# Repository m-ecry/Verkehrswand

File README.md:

# Verkehrswand
Einfache Anzeige für Ankunft und Abfahrt von einer Haltestelle mit Siebensegmentanzeigen und ein paar kleinen Extras.

- 2 Haltestellen
- 5 Linien
  - jeweils zwei Richtungen
  - Abfahrt in.., Nächste Abfahrt in..

Bauteilliste:
40x 7-Segmentanzeigen SC56-11GWA (Grün, 0,56") Common Cathode
40x Schieberegister SN74HC595
- pro Richtung 2x2 für Abfahrt in und nächste Abfahrt

1x Raspberry Pi (für Internetzugang, evtl. Austauschen durch Stromsparende Alternative)
X Knöpfe

Das ganze auf einer Holzplatte mit Abmaßen 75 x 55 cm, 5 cm hoch für Raum zum bestücken.
Jeden Tag ein wenig..
Und noch ein wenig..

SCHema und BoRDdateien, erstellt mit Eagle 7.7.0.
Enthalten Boardentwurf für 7-Segment Anzeige, angesteuert durch 2 74-595 Shift-Register. Nötige Anschlusskontaktierung: 
- Supply (1x GND, 1x VCC)
- SER
- CLK
- (optional) OE

Version A (doppelshift2): Standartversion mit Lötanschlüssen für Kontaktierung.

Version B (doppelshift2Bus): Kontaktierung über Flachbandkabel (6-adrig) dank Wannenstecker.

Idee für anderes Projekt: Pilzmonitor, Zeitschloss mit DC-Motor (Schrittmotor geeigneter?)

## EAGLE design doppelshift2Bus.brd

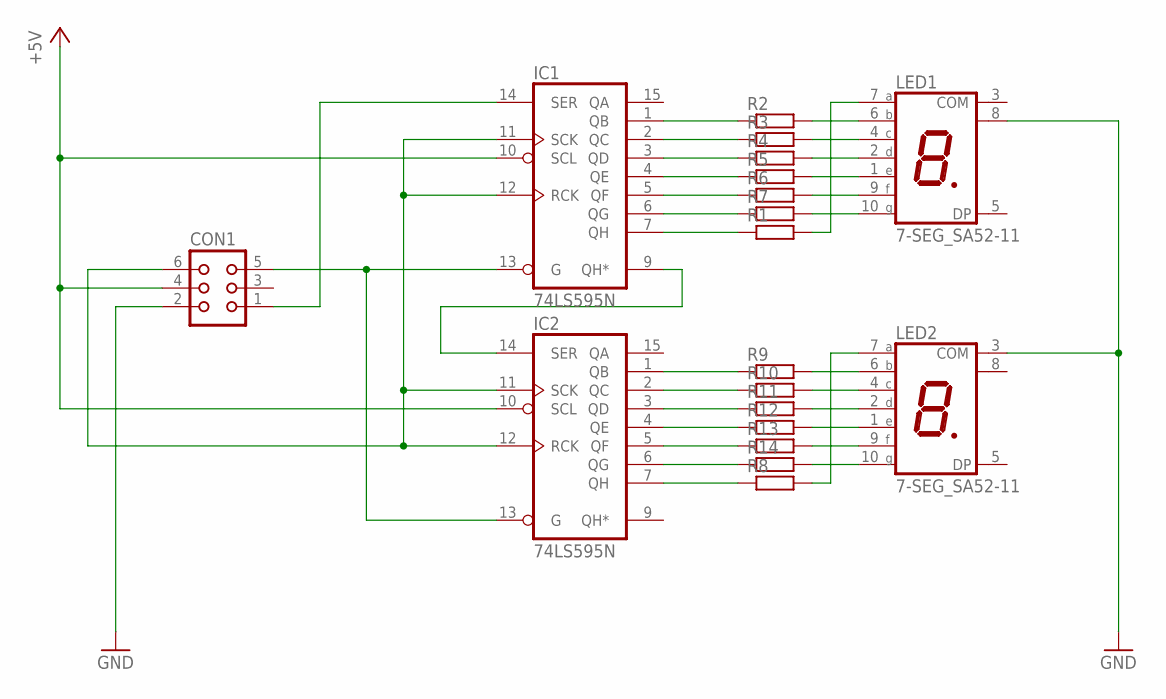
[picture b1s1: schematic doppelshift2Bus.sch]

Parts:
CON1: CON06L
IC1, IC2: 74LS595N; DIL16
LED1, LED2: 7-SEG_SA52-11; SA52-11
R1, R2, R3, R4, R5, R6, R7, R8, R9, R10, R11, R12, R13, R14: R-EU_0309/10; 0309/10

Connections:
CLK: CON1.6, IC1.11 (SCK), IC1.12 (RCK), IC2.11 (SCK), IC2.12 (RCK)
GND: CON1.2, IC1.8 (GND), IC2.8 (GND), LED1.8 (COM), LED2.3 (COM)
unnamed: IC2.7 (QH), R8.1
unnamed: IC1.1 (QB), R2.1
unnamed: IC1.2 (QC), R3.1
unnamed: IC1.3 (QD), R4.1
unnamed: IC1.4 (QE), R5.1
unnamed: IC1.5 (QF), R6.1
unnamed: IC1.6 (QG), R7.1
unnamed: LED2.7 (A), R8.2
unnamed: IC2.1 (QB), R9.1
unnamed: IC2.2 (QC), R10.1
unnamed: IC2.3 (QD), R11.1
unnamed: IC2.4 (QE), R12.1
unnamed: IC2.5 (QF), R13.1
unnamed: IC2.6 (QG), R14.1
unnamed: IC1.7 (QH), R1.1
unnamed: LED1.6 (B), R2.2
unnamed: LED1.4 (C), R3.2
unnamed: LED1.2 (D), R4.2
unnamed: LED1.1 (E), R5.2
unnamed: LED1.9 (F), R6.2
unnamed: LED1.10 (G), R7.2
unnamed: LED1.7 (A), R1.2
unnamed: LED2.6 (B), R9.2
unnamed: LED2.4 (C), R10.2
unnamed: LED2.2 (D), R11.2
unnamed: LED2.1 (E), R12.2
unnamed: LED2.9 (F), R13.2
unnamed: LED2.10 (G), R14.2
OE: CON1.5, IC1.13 (G), IC2.13 (G)
SER: CON1.1, IC1.14 (SER)
UBERTRAG: IC1.9 (QH*), IC2.14 (SER)
VCC: CON1.4, IC1.10 (SCL), IC1.16 (VCC), IC2.10 (SCL), IC2.16 (VCC)

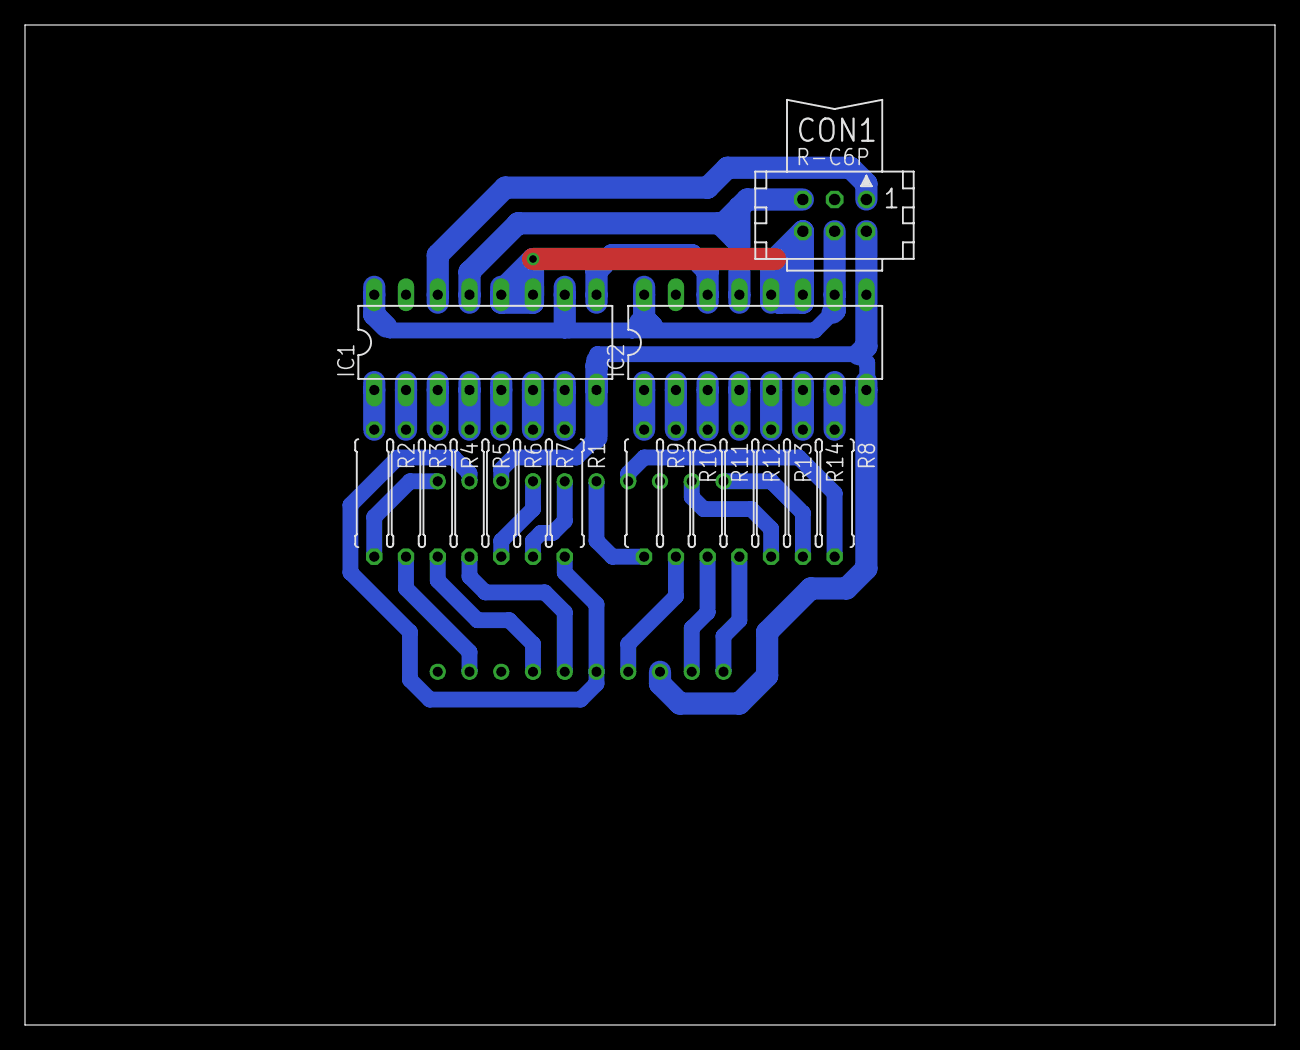
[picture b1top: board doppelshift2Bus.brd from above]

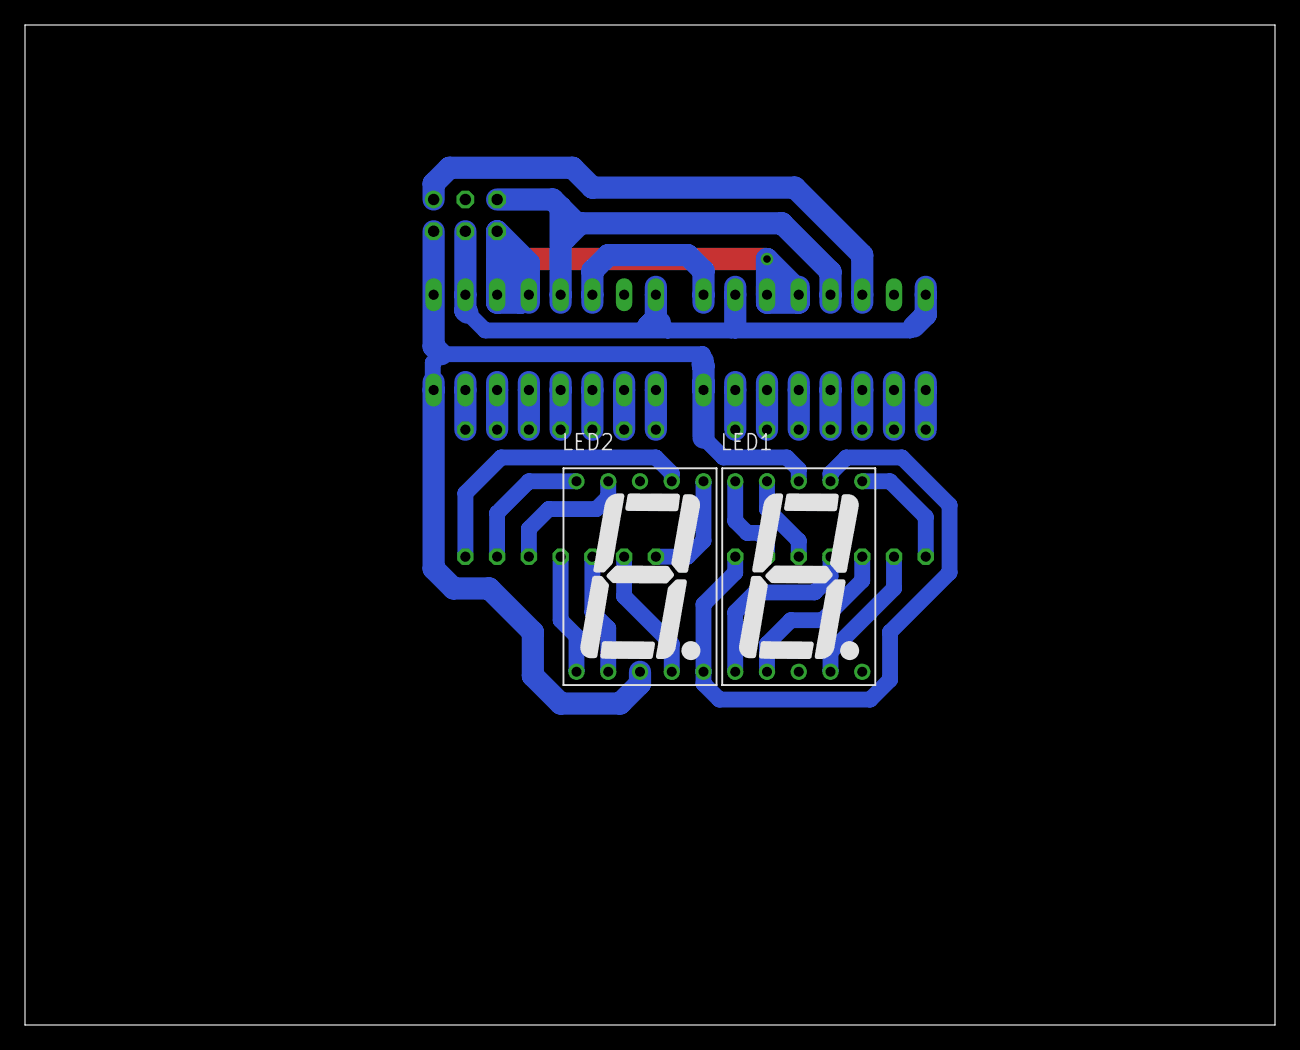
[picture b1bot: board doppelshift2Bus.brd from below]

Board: 2 copper layers, 100.0 x 80.0 mm, 19 parts (2 on the bottom side), 34 nets.

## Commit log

2016-07-08 Add files via upload
    Grobes Schema. Brauch besseres Programm...
2016-07-08 Add files via upload
    Käse, grobes Schema. Brauch besseres Programm
2016-07-12 Update README.md
    Bauteilliste (unvollständig) hinzugefügt
2016-07-16 Update README.md
    Projektfremdes reingeschrieben
2016-11-06 Add files via upload
    SCHema und BoRDdateien, erstellt mit Eagle 7.7.0.
    Enthalten Boardentwurf für 7-Segment Anzeige, angesteuert durch 2 74-595 Shift-Register. Nötige Anschlusskontaktierung:
    - Supply (1x GND, 1x VCC)
    - SER
    - CLK
    - (optional) OE
2016-11-06 Add files via upload
    Python-Skripte für aktualisierung der Daten von der Seite der Dd Verkehrsbetriebe.
    Nicht mehr getestet seit April 2016, womöglich unvollständig
